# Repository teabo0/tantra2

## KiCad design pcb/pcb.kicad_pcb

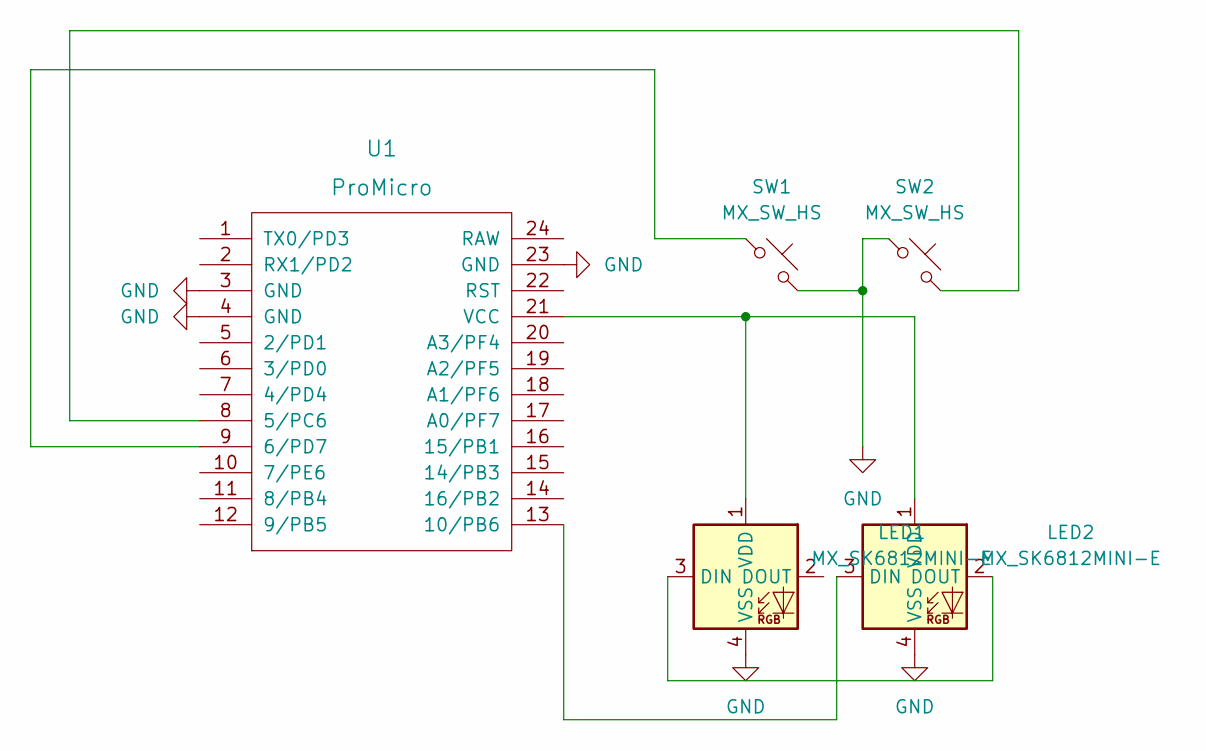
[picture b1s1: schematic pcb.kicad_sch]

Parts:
LED1, LED2: MX_SK6812MINI-E; LED_MX_6028R
SW1, SW2: MX_SW_HS; SW_MX_HS_1u
U1: ProMicro; ArduinoProMicro

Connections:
GND: LED1.4 (VSS), LED2.4 (VSS), SW1.2, SW2.1, U1.3 (GND), U1.4 (GND), U1.23 (GND)
unnamed: LED1.1 (VDD), LED2.1 (VDD), U1.21 (VCC)
unnamed: LED1.3 (DIN), LED2.2 (DOUT)
unnamed: LED2.3 (DIN), U1.13 (10/PB6)
unnamed: SW1.1, U1.9 (6/PD7)
unnamed: SW2.2, U1.8 (5/PC6)

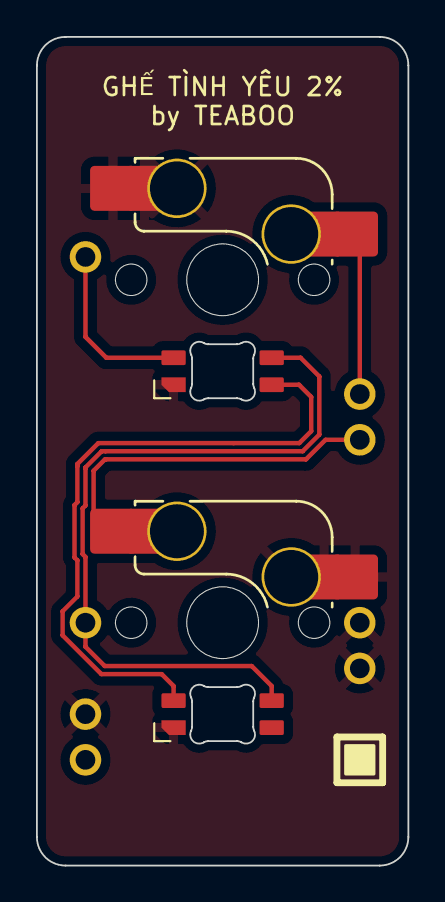
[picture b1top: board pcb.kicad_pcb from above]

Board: 2 copper layers, 20.6 x 46.0 mm, 5 parts (0 on the bottom side), 6 nets.

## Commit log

2022-09-21 basic pcb done
2022-09-21 basic pcb finished
2022-09-22 final board
2023-01-05 prototype board 2
2023-01-05 complete prototype 1
